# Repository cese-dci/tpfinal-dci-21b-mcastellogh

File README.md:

## Trabajo práctico final de la asignatura DCI ##
Este repositorio contiene el trabajo práctico final para la asignatura de Diseño de Circuitos Impresos de la carrera de posgrado de FIUBA.

* Autor: Marcelo Castello
* Título corto del trabajo:  LoRa End Device
* Descripción:  Implementación de dispositivo sensor de temperatiura con capa física LoRa/LoRaWAN con ESP8266

## Licencia de este trabajo ##
Licencia: [TAPR Open Hardware License](https://tapr.org/the-tapr-open-hardware-license)

[Enlace al archivo de texto de la misma](TAPR_Open_Hardware_License_v1.0.pdf)

## Estructura del TP FINAL ##

Se propone y se pide utilizar la siguiente estructura.

* doc: Toda la información sobre el circuito, principalmente de autoría o procesamiento propio. Por ejemplo:
  * Notas de ingeniería propias.
  * Notas de aplicación propias.
  * Estudios previos, estado del arte, resumen de las investigaciones.
  * Notas con cálculos.
  * Dibujos adicionales.
  * Fotos de los prototipos.
  * Presupuestos, cotizaciones.
* info: Toda la iformación recolectada, principalmente de terceros, como por ejemplo:
  * Hojas de datos.
  * Notas de aplicación.
  * Info de productos comerciales.
  * Info en internet.
* pcb: Archivos de diseño esquemático y pcb.

Dependiendo la magnitud del proyecto, tendremos más o menos información en estos directorios. 
Revisar los README.md en cada directorio para conocer las pautas de cada uno para este TP.

NOTA: El alumno puede y debe borrar de este archivo todo lo que considere necesario, por ejemplo las aclaraciones del docente y esta misma nota.

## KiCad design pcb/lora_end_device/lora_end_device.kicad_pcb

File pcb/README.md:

## Archivos Kicad ##

En este directorio se incluyen:

* Archivos de proyecto.
* Esquemático.
* PCB.
* Modelos  3D.
* Bibliotecas de símbolos y huellas externas (incluídos en el directorio [libs](libs))

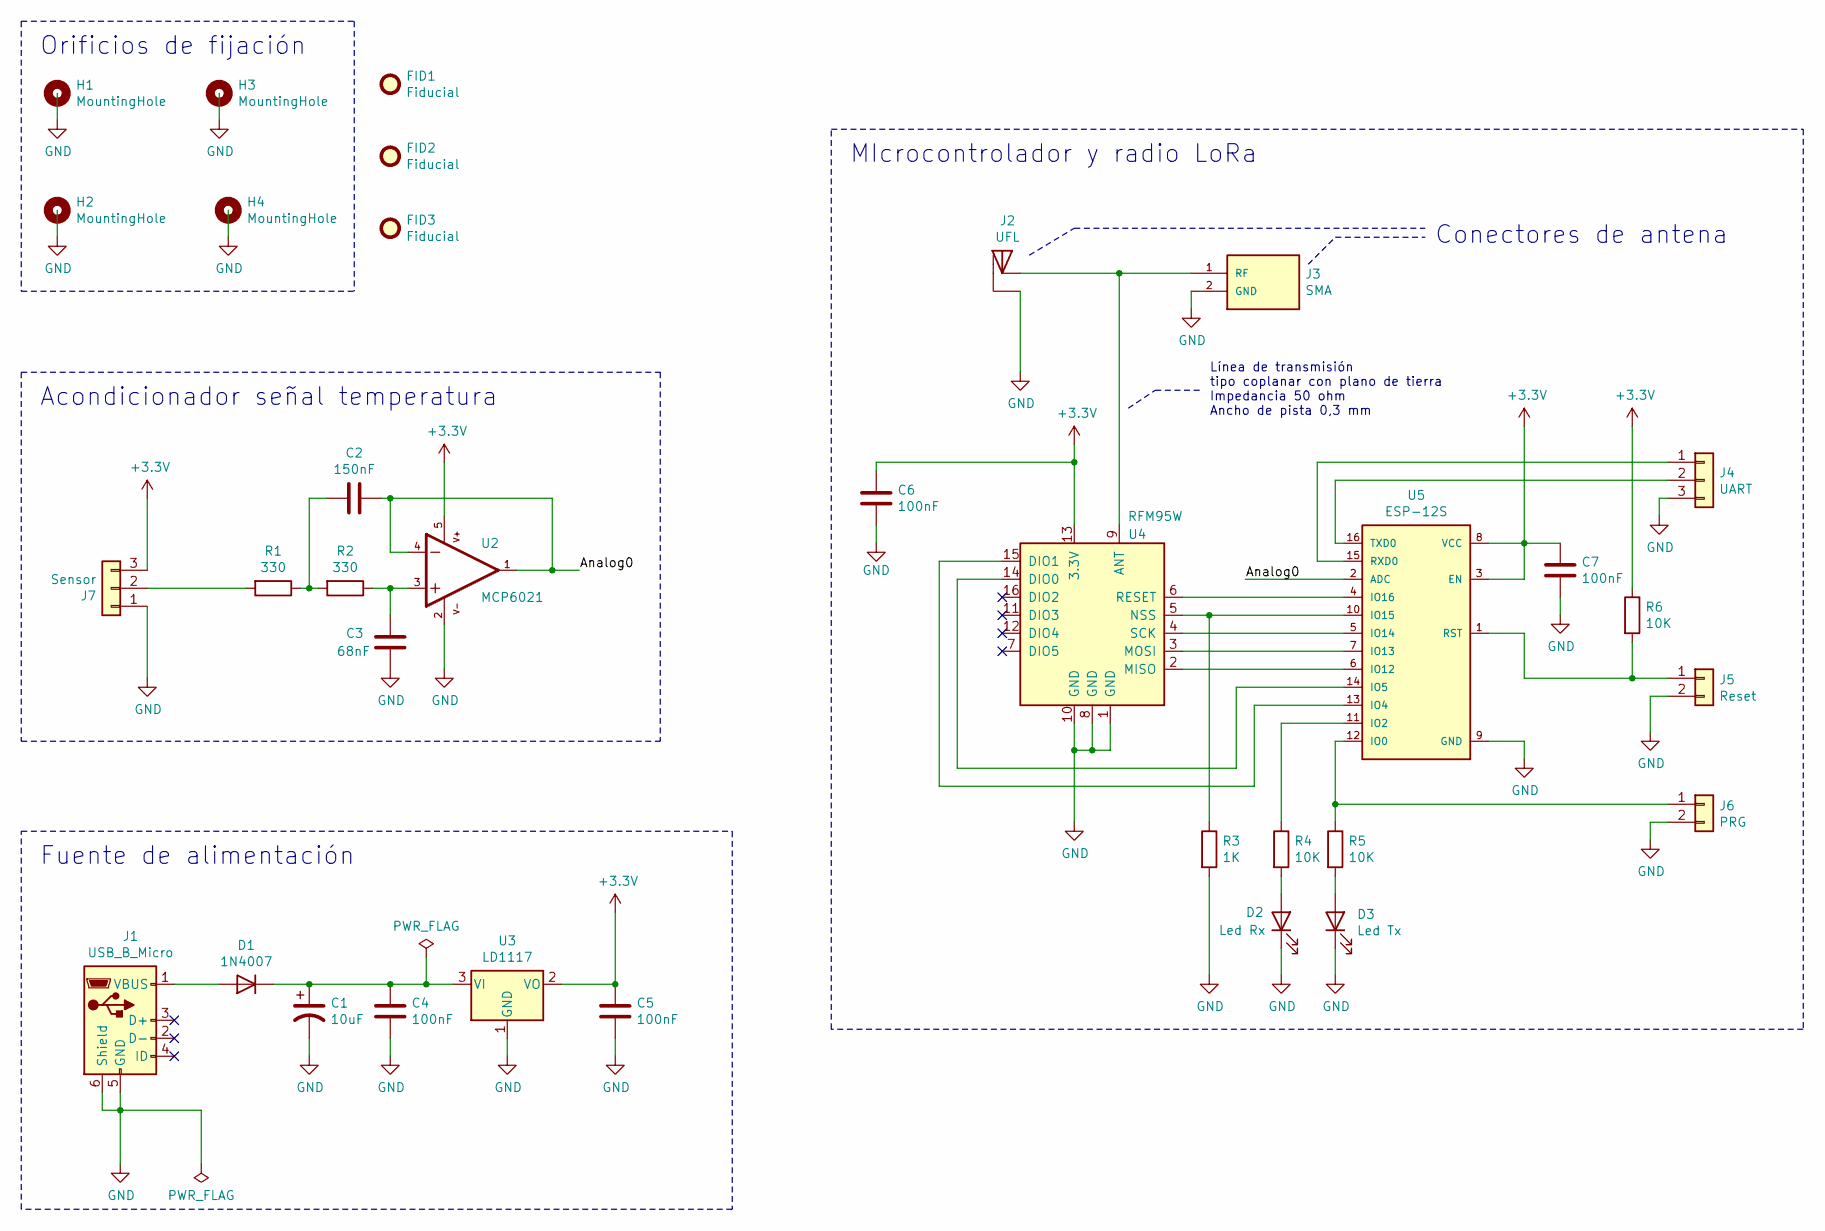
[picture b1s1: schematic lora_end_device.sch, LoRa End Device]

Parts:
C1: 10uF; CP_Elec_3x5.3
C2: 150nF; C_0805_2012Metric
C3: 68nF; C_0805_2012Metric
C4, C5, C6, C7: 100nF; C_0805_2012Metric
D1: 1N4007; D_1206_3216Metric
D2: Led Rx; LED_0805_2012Metric_Castellated; digikey# 350-4358-2-ND
D3: Led Tx; LED_0805_2012Metric_Castellated; digikey# 3372-0805RBD0070S01TR-ND
FID1, FID2, FID3: Fiducial; Fiducial_0.75mm_Mask1.5mm
H1, H2, H3, H4: MountingHole; MountingHole_2.5mm_Pad
J1: USB_B_Micro; USB_Mini-B_Lumberg_2486_01_Horizontal; digikey# 2057-MCR-B-S-RA-TSMT-NP-CS4-T/R-ND
J2: UFL; HRS_U.FL-R-SMT-1(10); digikey# CONUFL001-SMD-TTR-ND
J3: SMA; AMPHENOL_132203RP; PARTREV C; digikey# 732-13840-ND
J4: UART; PinHeader_1x03_P2.54mm_Vertical; digikey 2073-BC020-03-A-0200-0300-L-G-ND
J5: Reset; PinHeader_1x02_P2.54mm_Vertical; digikey 664-G800LF306018EU-ND
J6: PRG; PinHeader_1x02_P2.54mm_Vertical; digikey# 664-G800LF306018EU-ND
J7: Sensor; PinHeader_1x03_P2.54mm_Vertical; digikey# 2073-BC020-03-A-0200-0300-L-G-ND
R1, R2: 330; R_0805_2012Metric
R3: 1K; R_0805_2012Metric
R4, R5, R6: 10K; R_0805_2012Metric
U2: MCP6021; SOT23-5; digikey# MCP6021RT-E/OTTR-ND
U3: LD1117; SOT-223-3_TabPin2; digikey# 497-6447-2-ND
U4: RFM95W; HOPERF_RFM9XW_SMD; digikey# RFM95W-915S2-ND
U5: ESP-12S; digikey# ESP-12SRF-ND

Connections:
+3V3: C5.1, C6.1, C7.1, J7.3, R6.1, U2.5, U3.2 (VO), U4.13 (3.3V), U5.3 (EN), U5.8 (VCC)
/Analog0: C2.1, U2.1, U2.4, U5.2 (ADC)
GND: C1.2, C3.2, C4.2, C5.2, C6.2, C7.2, D2.1 (K), D3.1 (K), H1.1, H2.1, H3.1, H4.1, J1.5 (GND), J1.6 (Shield), J2.1, J3.2 (GND), J3.3, J3.4, J3.5, J4.3, J5.2, J6.2, J7.1, R3.2, U2.2, U3.1 (GND), U4.1 (GND), U4.8 (GND), U4.10 (GND), U5.9 (GND)
unnamed: C1.1, C4.1, D1.1 (K), U3.3 (VI)
unnamed: C2.2, R1.1, R2.2
unnamed: C3.1, R2.1, U2.3
unnamed: D1.2 (A), J1.1 (VBUS)
unnamed: D2.2 (A), R4.2
unnamed: D3.2 (A), R5.2
unnamed: J2.2, J3.1 (RF), U4.9 (ANT)
unnamed: J4.1, U5.15 (RXD0)
unnamed: J4.2, U5.16 (TXD0)
unnamed: J5.1, R6.2, U5.1 (RST)
unnamed: J6.1, R5.1, U5.12 (IO0)
unnamed: J7.2, R1.2
unnamed: R3.1, U4.5 (NSS), U5.10 (IO15)
unnamed: R4.1, U5.11 (IO2)
unnamed: U4.2 (MISO), U5.6 (IO12)
unnamed: U4.3 (MOSI), U5.7 (IO13)
unnamed: U4.4 (SCK), U5.5 (IO14)
unnamed: U4.6 (RESET), U5.4 (IO16)
unnamed: U4.14 (DIO0), U5.14 (IO5)
unnamed: U4.15 (DIO1), U5.13 (IO4)

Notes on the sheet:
Acondicionador señal temperatura
Fuente de alimentación
Conectores de antena
Orificios de fijación
MIcrocontrolador y radio LoRa
Línea de transmisión tipo coplanar con plano de tierra Impedancia 50 ohm Ancho de pista 0,3 mm

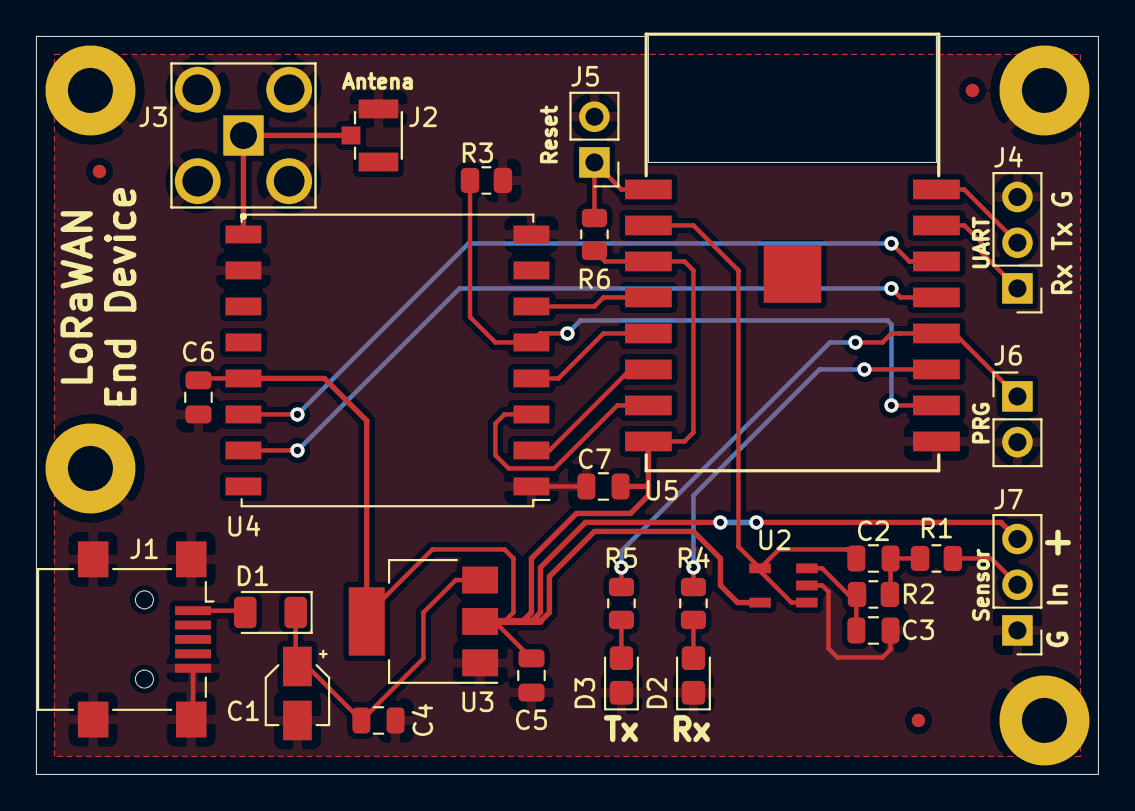
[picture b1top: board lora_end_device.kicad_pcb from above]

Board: 2 copper layers, 59.0 x 41.0 mm, 34 parts (0 on the bottom side), 23 nets.

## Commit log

2021-07-02 primer commit
2021-07-05 fix bugs ERC
2021-07-06 add asociaciones footprint, orificios fijacion
2021-07-21 correcciones de sugerencias revisor
2021-07-22 asociacion huellas, posicionamiento, borde
2021-07-27 add 3d models
2021-07-27 reubicacion de U5 y U4
2021-07-27 reubicacion U4, U5 add cotas
2021-07-29 reubicación de conector SMA
2021-08-03 add digikey part number
2021-08-10 add ruteo
2021-08-15 correcciones revisiones del docente
2021-08-17 Correcciones finales

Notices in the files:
pcb/lora_end_device/lora_end_device.kicad_pcb:
Licencia: TAPR Open Hardware Licence
